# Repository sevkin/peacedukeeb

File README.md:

# my DIY ergonomic keyboard prototype

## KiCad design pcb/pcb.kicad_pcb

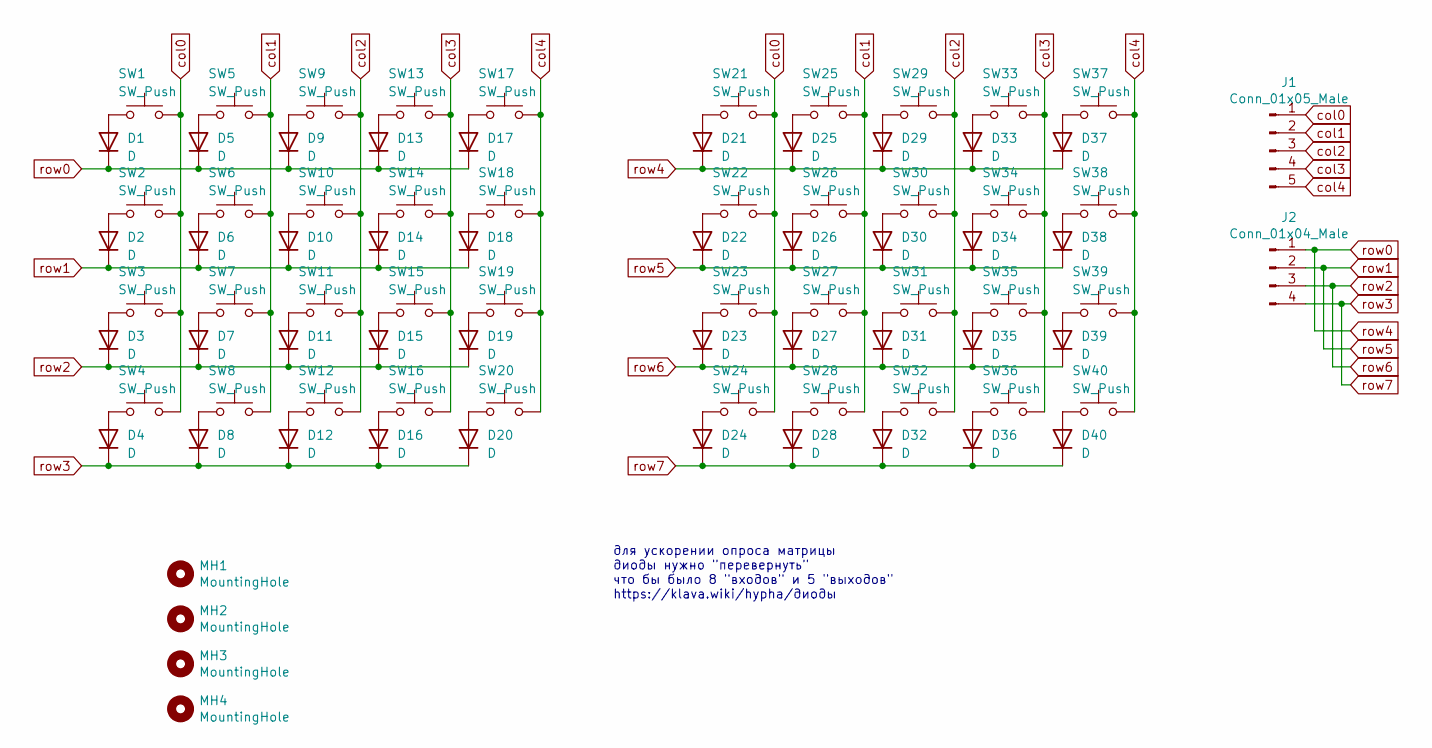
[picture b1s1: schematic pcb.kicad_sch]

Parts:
D1, D2, D3, D4, D5, D6, D7, D8, D9, D10, D11, D12, D13, D14, D15, D16, D17, D18, D19, D20, D21, D22, D23, D24, D25, D26, D27, D28, D29, D30, D31, D32, D33, D34, D35, D36, D37, D38, D39, D40: D; D_SOD-123
J1: Conn_01x05_Male; PinHeader_1x05_P2.54mm_Vertical
J2: Conn_01x04_Male; PinHeader_1x04_P2.54mm_Vertical
MH1, MH2, MH3, MH4: MountingHole; MountingHole_3.2mm_M3
SW1, SW2, SW3, SW4, SW5, SW6, SW7, SW8, SW9, SW10, SW11, SW12, SW13, SW14, SW15, SW16, SW17, SW18, SW19, SW20, SW21, SW22, SW23, SW24, SW25, SW26, SW27, SW28, SW29, SW30, SW31, SW32, SW33, SW34, SW35, SW36, SW37, SW38, SW39, SW40: SW_Push; Kailh_socket_MX

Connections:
unnamed: D1.2 (A), SW1.1
unnamed: D2.2 (A), SW2.1
unnamed: D3.2 (A), SW3.1
unnamed: D4.2 (A), SW4.1
unnamed: D5.2 (A), SW5.1
unnamed: D6.2 (A), SW6.1
unnamed: D7.2 (A), SW7.1
unnamed: D8.2 (A), SW8.1
unnamed: D9.2 (A), SW9.1
unnamed: D10.2 (A), SW10.1
unnamed: D11.2 (A), SW11.1
unnamed: D12.2 (A), SW12.1
unnamed: D13.2 (A), SW13.1
unnamed: D14.2 (A), SW14.1
unnamed: D15.2 (A), SW15.1
unnamed: D16.2 (A), SW16.1
unnamed: D17.2 (A), SW17.1
unnamed: D18.2 (A), SW18.1
unnamed: D19.2 (A), SW19.1
unnamed: D20.2 (A), SW20.1
unnamed: D21.2 (A), SW21.1
unnamed: D22.2 (A), SW22.1
unnamed: D23.2 (A), SW23.1
unnamed: D24.2 (A), SW24.1
unnamed: D25.2 (A), SW25.1
unnamed: D26.2 (A), SW26.1
unnamed: D27.2 (A), SW27.1
unnamed: D28.2 (A), SW28.1
unnamed: D29.2 (A), SW29.1
unnamed: D30.2 (A), SW30.1
unnamed: D31.2 (A), SW31.1
unnamed: D32.2 (A), SW32.1
unnamed: D33.2 (A), SW33.1
unnamed: D34.2 (A), SW34.1
unnamed: D35.2 (A), SW35.1
unnamed: D36.2 (A), SW36.1
unnamed: D37.2 (A), SW37.1
unnamed: D38.2 (A), SW38.1
unnamed: D39.2 (A), SW39.1
unnamed: D40.2 (A), SW40.1
col0: J1.1, SW1.2, SW2.2, SW3.2, SW4.2, SW21.2, SW22.2, SW23.2, SW24.2
col1: J1.2, SW5.2, SW6.2, SW7.2, SW8.2, SW25.2, SW26.2, SW27.2, SW28.2
col2: J1.3, SW9.2, SW10.2, SW11.2, SW12.2, SW29.2, SW30.2, SW31.2, SW32.2
col3: J1.4, SW13.2, SW14.2, SW15.2, SW16.2, SW33.2, SW34.2, SW35.2, SW36.2
col4: J1.5, SW17.2, SW18.2, SW19.2, SW20.2, SW37.2, SW38.2, SW39.2, SW40.2
row0: D1.1 (K), D5.1 (K), D9.1 (K), D13.1 (K), D17.1 (K), D21.1 (K), D25.1 (K), D29.1 (K), D33.1 (K), D37.1 (K), J2.1
row1: D2.1 (K), D6.1 (K), D10.1 (K), D14.1 (K), D18.1 (K), D22.1 (K), D26.1 (K), D30.1 (K), D34.1 (K), D38.1 (K), J2.2
row2: D3.1 (K), D7.1 (K), D11.1 (K), D15.1 (K), D19.1 (K), D23.1 (K), D27.1 (K), D31.1 (K), D35.1 (K), D39.1 (K), J2.3
row3: D4.1 (K), D8.1 (K), D12.1 (K), D16.1 (K), D20.1 (K), D24.1 (K), D28.1 (K), D32.1 (K), D36.1 (K), D40.1 (K), J2.4

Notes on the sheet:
для ускорении опроса матрицы диоды нужно "перевернуть" что бы было 8 "входов" и 5 "выходов" https://klava.wiki/hypha/диоды

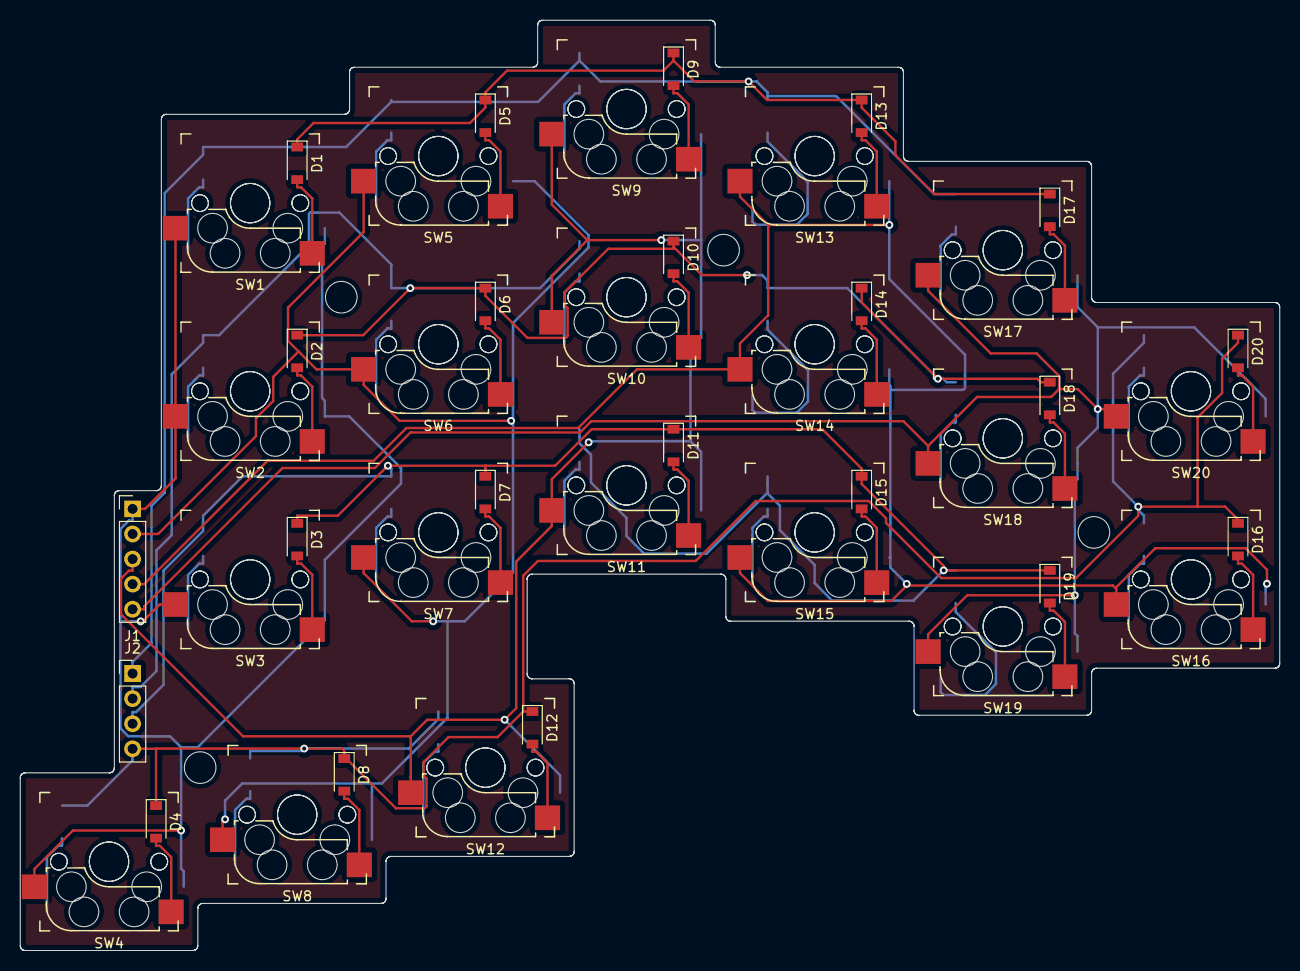
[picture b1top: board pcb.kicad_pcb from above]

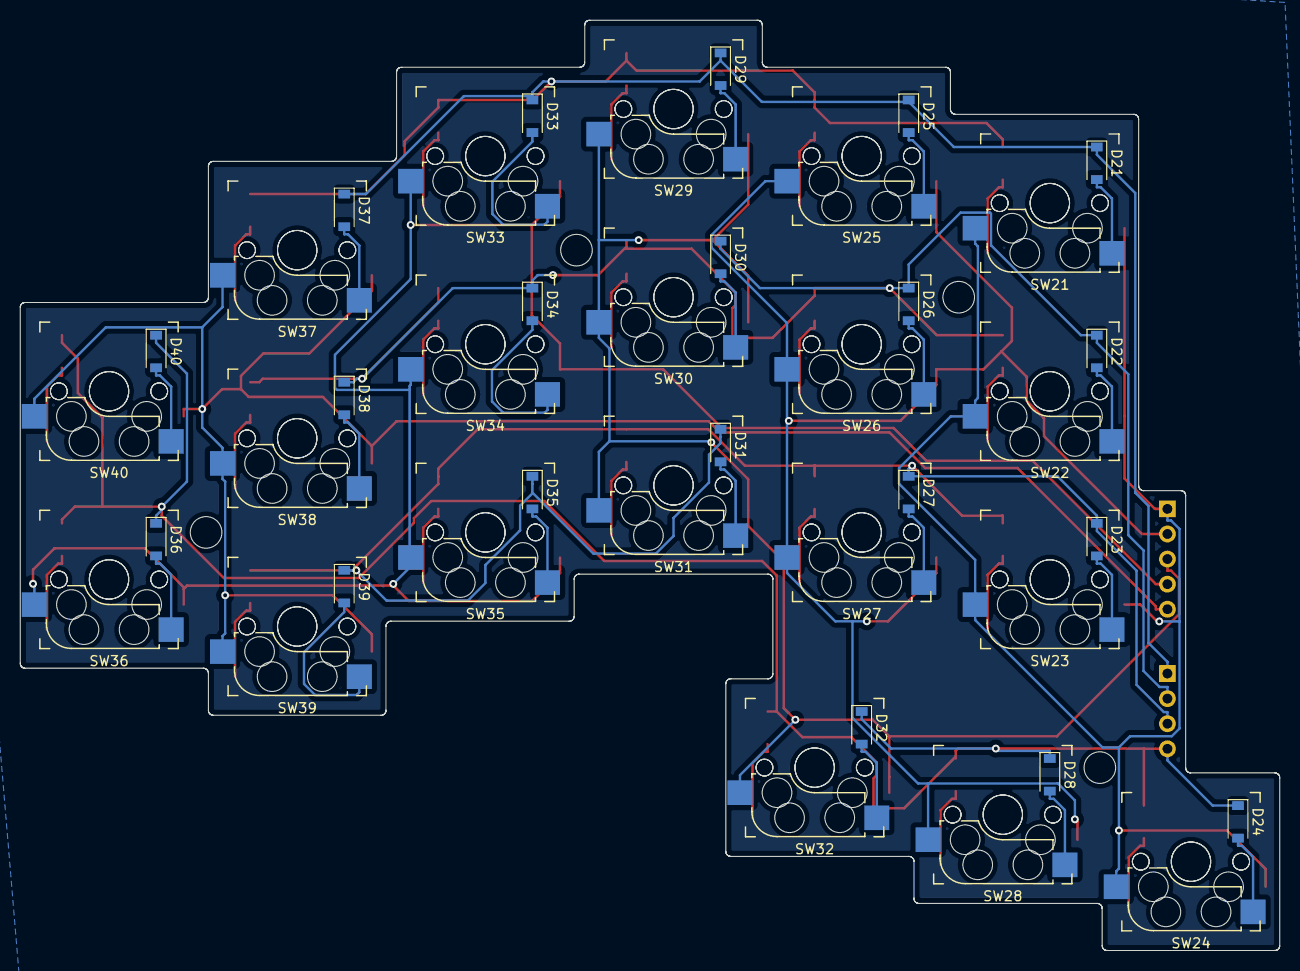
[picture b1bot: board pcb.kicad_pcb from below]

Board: 2 copper layers, 127.5 x 94.2 mm, 86 parts (40 on the bottom side), 49 nets.

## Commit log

2021-08-01 init
2021-08-01 cad [peaceduke]
2021-08-01 cad [zolotce]
2021-09-24 pcb split rows to front and back
    0..3 - front
    4..7 - back
2021-10-08 import mount holes from pcb to sch
2022-07-28 add diodes note, bump kicad 6
2022-11-06 fix bottom key outline
2024-06-09 kle files with "row,col" mark
